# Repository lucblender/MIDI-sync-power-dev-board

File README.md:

# MIDI-sync-power-dev-board

The MIDI-sync-power-dev-board is a 4hp eurorack module created to be used either as an expander for other board or as a standalone module helping you developping electronic.
The module provides :
- an isolated 5V 400mA
- a 3.3V 200mA from LDO
- a Sync in from 3.5mm jack (use as sync, gate, trigger, ...)
	- 0-xV signal input transformed to TTL level (signal is inverted)
- a MIDI input or MIDI output configurable through soldering jumper
	- Can only use one configuration at a time!

The module has a 2x a 10 pins header on top and bottom that gives you access to eurorack +12V and -12V, the board 5V and 3.3V, the Sync signal, the MIDI in or MIDI out signal. 

| Signal names|   |
|----------|---------|
| +5V      | +3.3V   |
| +12V     | -12V    |
| GND      | GND     |
| MIDI OUT | GND     |
| Sync IN  | MIDI IN |

The idea behind this module came while developping my own synth that needed MIDI input. I had to make my own little MIDI In through optocoupler on breadboard or veroboard each time. 

Additonally, I created the [Canvas](https://github.com/lucblender/simple_canvas) synthesizer in collaboration with [Synthux Academy](https://www.synthux.academy). And the board did not have MIDI input or sync in making it hard to sync with any synthesizer setup. To not add complexity to the design, I prefered to create this little expander that I now use to power the Canvas and use Sync in and MIDI input.

## Schematic

## PCB

|Top|Bottom|
|----|----|
|||

### MIDI configuration

|MIDI in|MIDI out|
|----|----|
|On the bottom, you need to solder JP1 and JP2|On the top, you need to solder JP3, JP4 and JP5|

*Reminder*: You can only use one MIDI configuration at a time!

## Front panel

The MIDI-sync-power-dev-board has mutliple front panel since it can be use for various reason.
- midi-sync-module-front-panel-**a**: Dedicated to the Canvas
- midi-sync-module-front-panel-**b**: Generic Sync In, MIDI OUT
- midi-sync-module-front-panel-**c**: Generic Sync In, MIDI IN

All the front panel are double sided. On the Top you will find a the debug front panel with 10 pins header description. And on the Bottom you will find the custom design.

### Front Panel Example

| front-panel-**a**-top|front-panel-**a**-bottom|front-panel-**b**-top|front-panel-**b**-bottom|front-panel-**c**-top|front-panel-**c**-bottom|
|----|----|----|----|----|----|
||TODO||||||

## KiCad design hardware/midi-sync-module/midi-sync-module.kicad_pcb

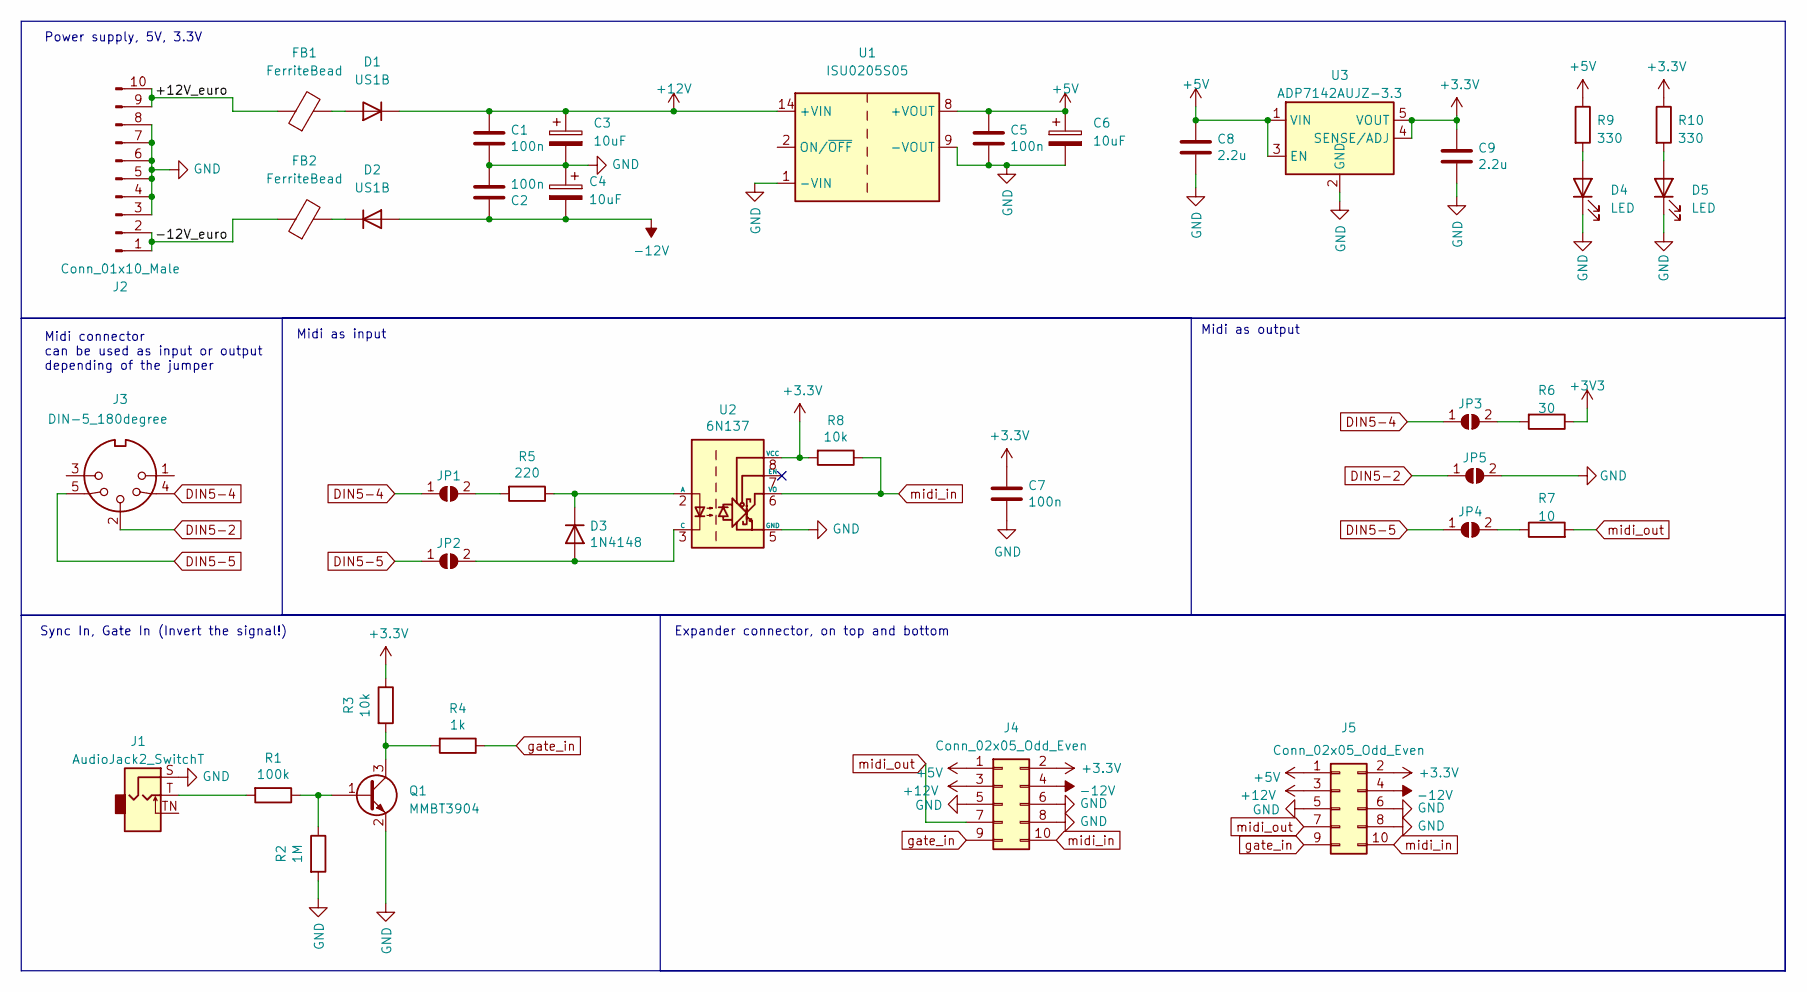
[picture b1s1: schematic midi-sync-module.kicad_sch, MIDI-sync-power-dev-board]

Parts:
C1, C2, C5, C7: 100n; C_0603_1608Metric; LCSC C14663
C3, C4, C6: 10uF; CP_Elec_6.3x5.9
C8, C9: 2.2u; C_0805_2012Metric; LCSC C14663
D1, D2: US1B; D_SMA
D3: 1N4148; D_SOD-123; LCSC C81598
D4, D5: LED; LED_D3.0mm
FB1, FB2: FerriteBead; L_0805_2012Metric
J1: AudioJack2_SwitchT; Jack_3.5mm_QingPu_WQP-PJ301BM_Vertical
J2: Conn_01x10_Male; PinHeader_2x05_P2.54mm_Vertical
J3: DIN-5_180degree; CUI_SD-50BV
J4: Conn_02x05_Odd_Even; PinHeader_2x05_P2.54mm_Vertical_SMD
J5: Conn_02x05_Odd_Even; PinHeader_2x05_P2.54mm_Horizontal
JP1, JP2, JP3, JP4, JP5: SolderJumper_2_Open; SolderJumper-2_P1.3mm_Open_Pad1.0x1.5mm
Q1: MMBT3904; SOT-23
R1: 100k; R_0603_1608Metric; LCSC C22962
R2: 1M; R_0603_1608Metric; LCSC C22962
R3: 10k; R_0603_1608Metric; LCSC C22962
R4: 1k; R_0603_1608Metric; LCSC C22962
R5: 220; R_0603_1608Metric; LCSC C22962
R6: 30; R_0805_2012Metric
R7: 10; R_0805_2012Metric
R8: 10k; R_0603_1608Metric; LCSC C25804
R9, R10: 330; R_0805_2012Metric
U1: ISU0205S05; Converter_DCDC_XP_POWER-ISU02_SMD
U2: 6N137; SMDIP-8_W9.53mm; LCSC C110020
U3: ADP7142AUJZ-3.3; TSOT-23-5

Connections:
+5V: C5.1, C6.1, C8.1, J4.1, J5.1, R9.1, U1.8 (+VOUT), U3.1 (VIN), U3.3 (EN)
+12V: C1.1, C3.1, D1.1 (K), J4.3, J5.3, U1.14 (+VIN)
-12V: C2.1, C4.2, D2.2 (A), J4.4, J5.4
/+12V_euro: FB1.1, J2.9, J2.10
/-12V_euro: FB2.1, J2.1, J2.2
DIN5-2: J3.2, JP5.1 (A)
DIN5-4: J3.4, JP1.1 (A), JP3.1 (A)
DIN5-5: J3.5, JP2.1 (A), JP4.1 (A)
GND: C1.2, C2.2, C3.2, C4.1, C5.2, C6.2, C7.2, C8.2, C9.2, D4.1 (K), D5.1 (K), J1.S, J2.3, J2.4, J2.5, J2.6, J2.7, J2.8, J4.5, J4.6, J4.8, J5.5, J5.6, J5.8, JP5.2 (B), Q1.2 (E), R2.2, U1.1 (-VIN), U1.9 (-VOUT), U2.5 (GND), U3.2 (GND)
unnamed: D1.2 (A), FB1.2
unnamed: D2.1 (K), FB2.2
unnamed: D3.2 (A), JP2.2 (B), U2.3 (C)
unnamed: D3.1 (K), R5.1, U2.2 (A)
unnamed: D4.2 (A), R9.2
unnamed: D5.2 (A), R10.2
unnamed: J1.T, R1.2
unnamed: JP1.2 (B), R5.2
unnamed: JP3.2 (B), R6.2
unnamed: JP4.2 (B), R7.1
unnamed: Q1.1 (B), R1.1, R2.1
unnamed: Q1.3 (C), R3.2, R4.2
gate_in: J4.9, J5.9, R4.1
midi_in: J4.10, J5.10, R8.1, U2.6 (VO)
midi_out: J4.7, J5.7, R7.2

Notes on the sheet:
Midi connector can be used as input or output depending of the jumper
Midi as output
Expander connector, on top and bottom
Midi as input
Power supply, 5V, 3.3V
Sync In, Gate In (Invert the signal!)

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
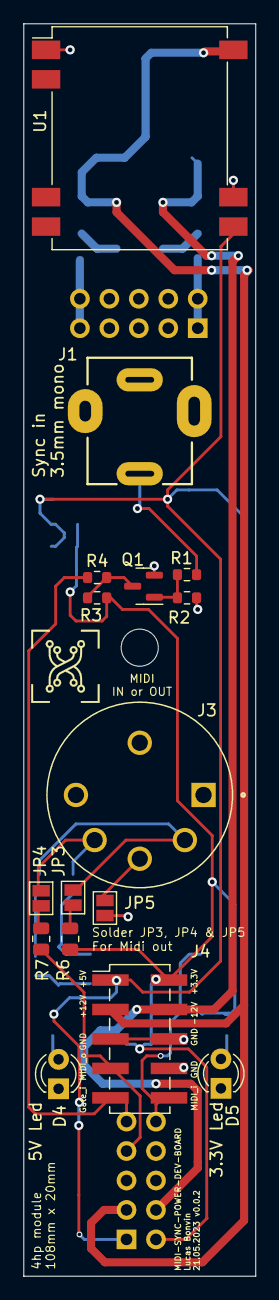
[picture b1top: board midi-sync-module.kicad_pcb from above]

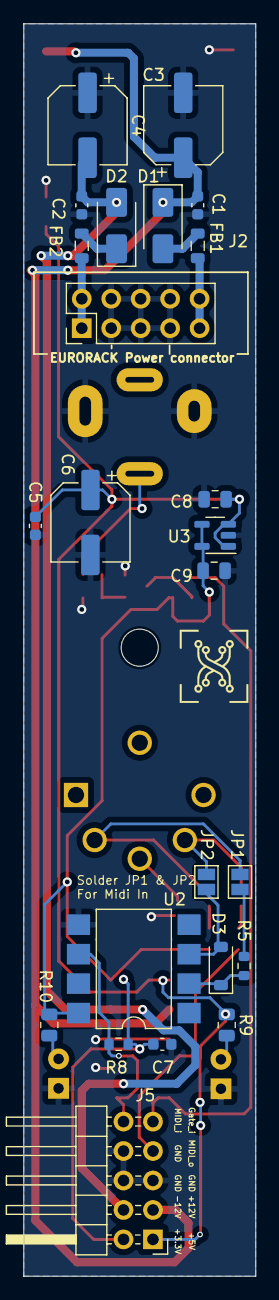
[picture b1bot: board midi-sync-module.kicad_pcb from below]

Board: 2 copper layers, 20.0 x 108.0 mm, 40 parts (24 on the bottom side), 25 nets.

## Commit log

2023-05-21 add gitignore and pictures files in lfs
2023-05-21 add main pcb
2023-05-21 add front panel a
2023-05-21 add front panel b
2023-05-21 add front panel c
2023-05-21 remove design files from git
2023-05-21 add pictures
2023-05-21 update pbc to v0.0.2 (fix polarized cap C3 and some texts) and panel c
2023-05-21 why do I keep putting to n to panel
2023-05-21 Started readme
